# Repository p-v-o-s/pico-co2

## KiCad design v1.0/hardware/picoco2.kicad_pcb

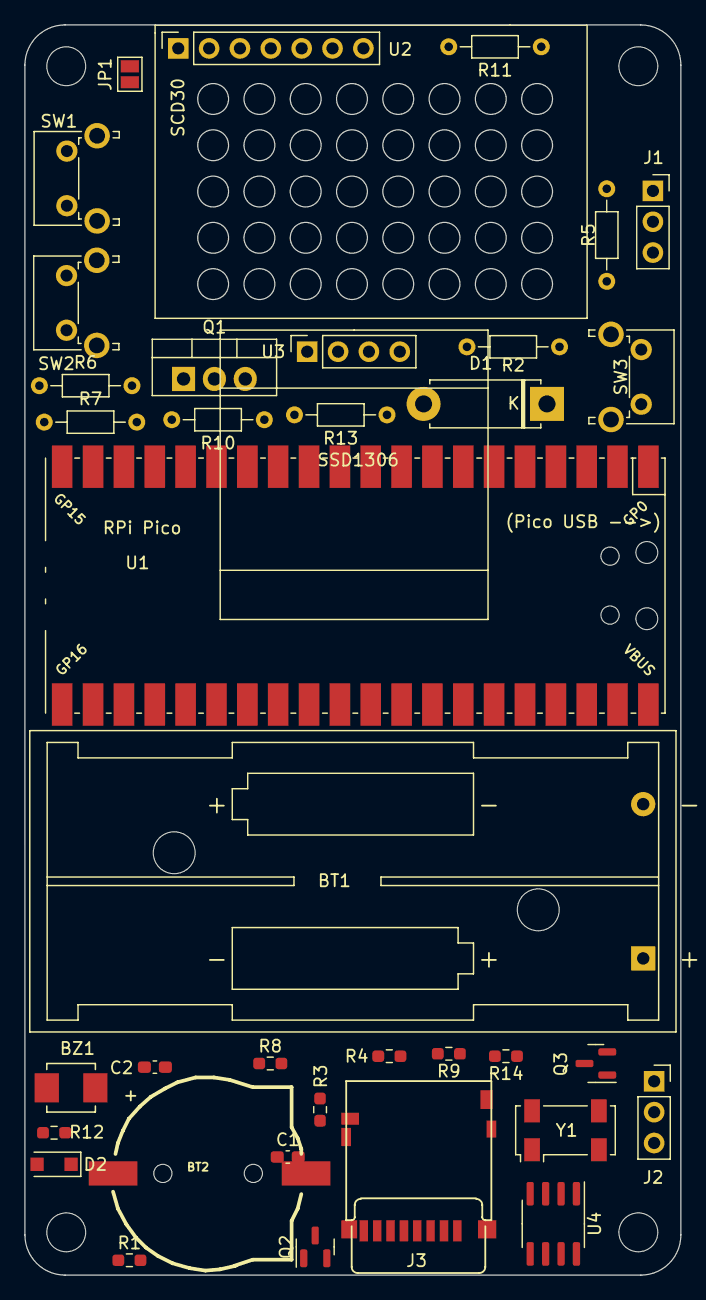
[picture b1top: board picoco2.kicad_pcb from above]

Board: 2 copper layers, 54.0 x 102.9 mm, 40 parts (0 on the bottom side), 24 nets, no tracks yet.

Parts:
BT1: Battery; BatteryHolder_Keystone_2468_2xAAA
BT2: CR1220; CR1220-2
BZ1: Buzzer; CUI_CMT-4023S-SMT-TR
C1, C2: 10uF; C_0603_1608Metric_Pad1.08x0.95mm_HandSolder
D1: D; D_5W_P10.16mm_Horizontal
D2: D; D_SOD-123F
H1, H2, H3, H4: MountingHole; MountingHole_3.2mm_M3
J1, J2: Conn_01x03_Female; PinSocket_1x03_P2.54mm_Vertical
J3: Micro_SD_Card; DM3D-SF_outline
JP1: SolderJumper_2_Open; SolderJumper-2_P1.3mm_Open_Pad1.0x1.5mm
Q1: Q_PMOS_GDS; TO-220-3_Vertical
Q2, Q3: Q_PMOS_GSD; SOT-23
R1, R3, R4: 4.7K; R_0603_1608Metric_Pad0.98x0.95mm_HandSolder
R2, R5: 4.7K; R_Axial_DIN0204_L3.6mm_D1.6mm_P7.62mm_Horizontal
R6, R7, R10, R11, R13: 10K; R_Axial_DIN0204_L3.6mm_D1.6mm_P7.62mm_Horizontal
R8, R12, R14: 10K; R_0603_1608Metric_Pad0.98x0.95mm_HandSolder
R9: 1K; R_0603_1608Metric_Pad0.98x0.95mm_HandSolder
SW1, SW2, SW3: SW_Push; SW_Tactile_SPST_Angled_PTS645Vx31-2LFS
U1: PicoW; RPi_PicoW_SMD
U2: scd30; scd30_a
U3: ssd1306; ssd1306_b
U4: PCF8523T; SOIC-8_3.9x4.9mm_P1.27mm
Y1: 32KHz; Crystal_SMD_Abracon_ABS25-4Pin_8.0x3.8mm

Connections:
+3V3: C2.1, J3.4 (VDD), R2.1, R3.1, R4.1, R5.1, R6.1, R7.1, R9.2, R10.1, R11.1, R13.1, R14.1, U1.36 (3V3), U2.1 (3v3), U3.2 (3V3)
BUT_A: R6.2, R7.2, R10.2, R11.2, SW1.1, SW2.1, U1.5 (GPIO3)
BUT_B: R13.2, R14.2, SW3.1, U1.6 (GPIO4)
GND: BT1.2 (-), BT2.2 (-), C1.2, C2.2, J3.6 (VSS), JP1.1 (A), Q3.3 (D), R1.2, R8.2, R12.2, SW1.2, SW2.2, SW3.2, U1.3 (GND), U3.1 (GND), U4.4 (VSS)
MISO: J3.7 (DAT0), U1.16 (GPIO12)
MOSI: J3.3 (CMD), U1.15 (GPIO11)
unnamed: BT2.1 (+), U4.3 (VBAT)
unnamed: C1.1, R9.1, U4.8 (VDD)
unnamed: J1.3, R1.1
unnamed: J2.2, R8.1
unnamed: U4.1 (OSCI), Y1.4
unnamed: U4.2 (OSCO), Y1.1
PI_EN: J1.2, U1.37 (3V3_EN)
RTC_INT: U1.11 (GPIO8), U4.7 (~INT1/CLKOUT)
SCD30_EN: Q3.1 (G), R12.1, U1.7 (GPIO5)
SCD30_GND: JP1.2 (B), Q3.2 (S), U2.2 (GND)
SCK: J3.5 (CLK), U1.14 (GPIO10)
SCL: R4.2, R5.2, U1.2 (GPIO1), U2.3 (SCL), U3.3 (SCL), U4.6 (SCL)
SDA: R2.2, R3.2, U1.1 (GPIO0), U2.4 (SDA), U3.4 (SDA), U4.5 (SDA)
SD_CS: J3.2 (DAT3/CD), U1.4 (GPIO2)
VBAT_AAA: BT1.1 (+), D1.2 (A), D2.2 (A), Q1.2 (D), Q2.3 (D)
VBUS: Q1.1 (G), Q2.1 (G), U1.40 (VBUS)
VSYS: D1.1 (K), D2.1 (K), Q1.3 (S), Q2.2 (S), U1.39 (VSYS)
WRITE_EN: J2.3, U1.9 (GPIO6)

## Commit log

2023-03-04 add code with AIO, sparkline plot.
2023-03-05 restructure directories, use settings.toml, add error handling
2023-03-05 Move splash screen first, set RTC using NTP
2023-03-05 send data to adafruitio every 30s plot every 2s
2023-03-08 add bayou logging
